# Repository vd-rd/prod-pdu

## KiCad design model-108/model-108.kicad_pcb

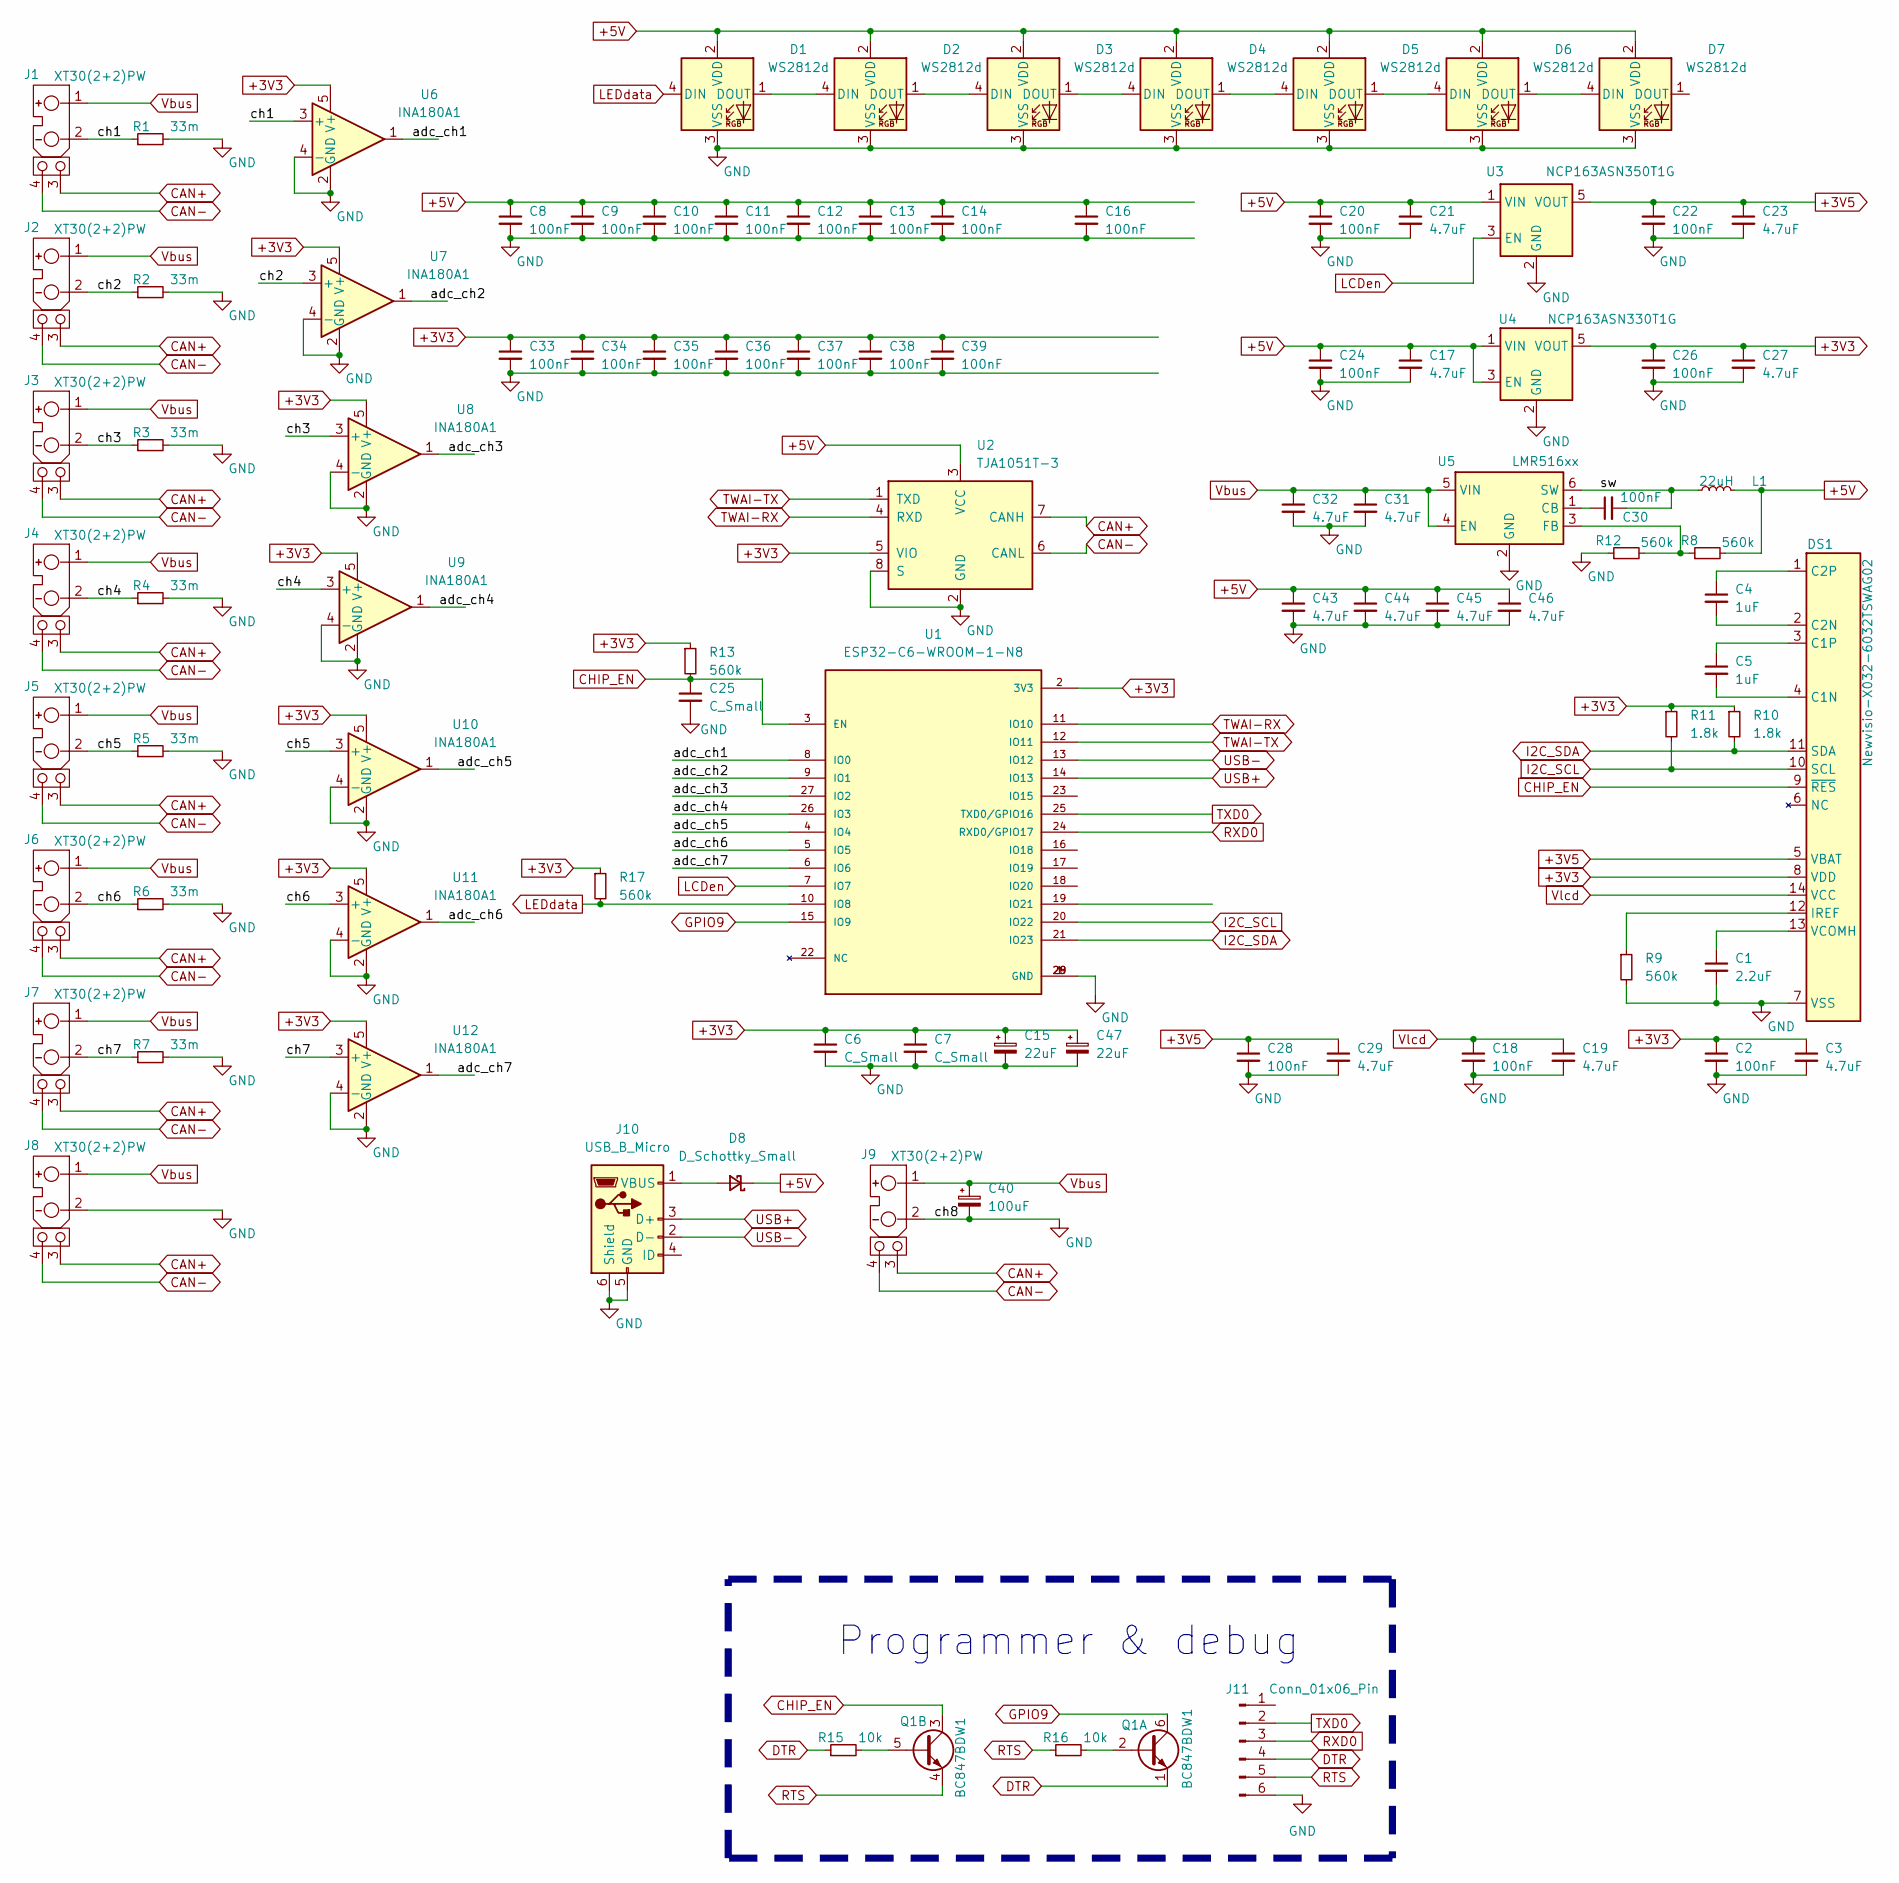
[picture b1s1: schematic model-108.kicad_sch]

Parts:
C1: 2.2uF; C_0603_1608Metric
C2, C8, C9, C10, C11, C12, C13, C14, C16, C18, C20, C22, C24, C26, C28, C30, C33, C34, C35, C36, C37, C38, C39: 100nF; C_0603_1608Metric
C3, C17, C19, C21, C23, C27, C29: 4.7uF; C_0603_1608Metric
C4, C5: 1uF; C_0603_1608Metric; Voltage 16V
C6, C7, C25: C_Small; C_0603_1608Metric
C15, C47: 22uF; CP_EIA-3216-10_Kemet-I
C31, C32, C43, C44, C45, C46: 4.7uF; C_0805_2012Metric
C40: 100uF; CP_Elec_8x5.4
D1, D2, D3, D4, D5, D6, D7: WS2812d; LED_D5.0mm-4_RGB
D8: D_Schottky_Small; D_SOD-123
DS1: Newvisio-X032-6032TSWAG02; OLED-60032D
J1, J2, J3, J4, J5, J6, J7, J8, J9: XT30(2+2)PW; AMASS_XT30(2+2)PW-M_P2.50mm_Horizontal
J10: USB_B_Micro; USB_Micro-B_Amphenol_10103594-0001LF_Horizontal
J11: Conn_01x06_Pin; PinHeader_1x06_P2.54mm_Vertical
L1: 22uH; L_Bourns_SRN8040TA
Q1: BC847BDW1; SOT-363_SC-70-6
R1, R2, R3, R4, R5, R6, R7: 33m; R_2512_6332Metric
R8, R9, R12, R13, R17: 560k; R_0603_1608Metric
R10, R11: 1.8k; R_0603_1608Metric
R15, R16: 10k; R_0402_1005Metric
U1: ESP32-C6-WROOM-1-N8; XCVR_ESP32-C6-WROOM-1-N8; PARTREV 1.0
U2: TJA1051T-3; SOIC-8_3.9x4.9mm_P1.27mm
U3: NCP163ASN350T1G; SOT-23-5
U4: NCP163ASN330T1G; SOT-23-5
U5: LMR516xx; TSOT-23-6
U6, U7, U8, U9, U10, U11, U12: INA180A1; SOT-23-5

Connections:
+3V3: C2.1, C3.1, C6.1, C7.1, C15.1, C26.1, C27.1, C33.1, C34.1, C35.1, C36.1, C37.1, C38.1, C39.1, C47.1, DS1.8 (VDD), R10.1, R11.1, R13.1, R17.1, U1.2 (3V3), U2.5 (VIO), U4.5 (VOUT), U6.5 (V+), U7.5 (V+), U8.5 (V+), U9.5 (V+), U10.5 (V+), U11.5 (V+), U12.5 (V+)
+3V5: C22.1, C23.1, C28.1, C29.1, DS1.5 (VBAT), U3.5 (VOUT)
+5V: C8.1, C9.1, C10.1, C11.1, C12.1, C13.1, C14.1, C16.1, C17.1, C20.1, C21.1, C24.1, C43.1, C44.1, C45.1, C46.1, D1.2 (VDD), D2.2 (VDD), D3.2 (VDD), D4.2 (VDD), D5.2 (VDD), D6.2 (VDD), D7.2 (VDD), D8.1 (K), L1.1, R8.2, U2.3 (VCC), U3.1 (VIN), U4.1 (VIN), U4.3 (EN)
/adc_ch1: U1.8 (IO0), U6.1
/adc_ch2: U1.9 (IO1), U7.1
/adc_ch3: U1.27 (IO2), U8.1
/adc_ch4: U1.26 (IO3), U9.1
/adc_ch5: U1.4 (IO4), U10.1
/adc_ch6: U1.5 (IO5), U11.1
/adc_ch7: U1.6 (IO6), U12.1
/ch1: J1.2, R1.1, U6.3 (+)
/ch2: J2.2, R2.1, U7.3 (+)
/ch3: J3.2, R3.1, U8.3 (+)
/ch4: J4.2, R4.1, U9.3 (+)
/ch5: J5.2, R5.1, U10.3 (+)
/ch6: J6.2, R6.1, U11.3 (+)
/ch7: J7.2, R7.1, U12.3 (+)
/sw: C30.2, L1.2, U5.6 (SW)
CAN+: J1.3, J2.3, J3.3, J4.3, J5.3, J6.3, J7.3, J8.3, J9.3, U2.7 (CANH)
CAN-: J1.4, J2.4, J3.4, J4.4, J5.4, J6.4, J7.4, J8.4, J9.4, U2.6 (CANL)
CHIP_EN: C25.1, DS1.9 (~RES), Q1.3 (C2), R13.2, U1.3 (EN)
DTR: J11.4, Q1.1 (E1), R15.1
GND: C1.2, C2.2, C3.2, C6.2, C7.2, C8.2, C9.2, C10.2, C11.2, C12.2, C13.2, C14.2, C15.2, C16.2, C17.2, C18.2, C19.2, C20.2, C21.2, C22.2, C23.2, C24.2, C25.2, C26.2, C27.2, C28.2, C29.2, C31.2, C32.2, C33.2, C34.2, C35.2, C36.2, C37.2, C38.2, C39.2, C40.2, C43.2, C44.2, C45.2, C46.2, C47.2, D1.3 (VSS), D2.3 (VSS), D3.3 (VSS), D4.3 (VSS), D5.3 (VSS), D6.3 (VSS), D7.3 (VSS), DS1.7 (VSS), J8.2, J9.2, J10.5 (GND), J10.6 (Shield), J11.6, R1.2, R2.2, R3.2, R4.2, R5.2, R6.2, R7.2, R9.2, R12.1, U1.1 (GND), U1.28 (GND), U1.29 (GND), U2.2 (GND), U2.8 (S), U3.2 (GND), U4.2 (GND), U5.2 (GND), U6.2 (GND), U6.4 (-), U7.2 (GND), U7.4 (-), U8.2 (GND), U8.4 (-), U9.2 (GND), U9.4 (-), U10.2 (GND), U10.4 (-), U11.2 (GND), U11.4 (-), U12.2 (GND), U12.4 (-)
GPIO9: Q1.6 (C1), U1.15 (IO9)
I2C_SCL: DS1.10 (SCL), R11.2, U1.20 (IO22)
I2C_SDA: DS1.11 (SDA), R10.2, U1.21 (IO23)
LCDen: U1.7 (IO7), U3.3 (EN)
LEDdata: D1.4 (DIN), R17.2, U1.10 (IO8)
unnamed: D1.1 (DOUT), D2.4 (DIN)
unnamed: D2.1 (DOUT), D3.4 (DIN)
unnamed: D3.1 (DOUT), D4.4 (DIN)
unnamed: D4.1 (DOUT), D5.4 (DIN)
unnamed: D5.1 (DOUT), D6.4 (DIN)
unnamed: D6.1 (DOUT), D7.4 (DIN)
unnamed: D8.2 (A), J10.1 (VBUS)
unnamed: C5.2, DS1.4 (C1N)
unnamed: C5.1, DS1.3 (C1P)
unnamed: C4.2, DS1.2 (C2N)
unnamed: C4.1, DS1.1 (C2P)
unnamed: DS1.12 (IREF), R9.1
unnamed: C1.1, DS1.13 (VCOMH)
unnamed: Q1.2 (B1), R16.2
unnamed: Q1.5 (B2), R15.2
unnamed: C30.1, U5.1 (CB)
unnamed: R8.1, R12.2, U5.3 (FB)
RTS: J11.5, Q1.4 (E2), R16.1
RXD0: J11.3, U1.24 (RXD0/GPIO17)
TWAI-RX: U1.11 (IO10), U2.4 (RXD)
TWAI-TX: U1.12 (IO11), U2.1 (TXD)
TXD0: J11.2, U1.25 (TXD0/GPIO16)
USB+: J10.3 (D+), U1.14 (IO13)
USB-: J10.2 (D-), U1.13 (IO12)
Vbus: C31.1, C32.1, C40.1, J1.1, J2.1, J3.1, J4.1, J5.1, J6.1, J7.1, J8.1, J9.1, U5.4 (EN), U5.5 (VIN)
Vlcd: C18.1, C19.1, DS1.14 (VCC)

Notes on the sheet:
Programmer & debug

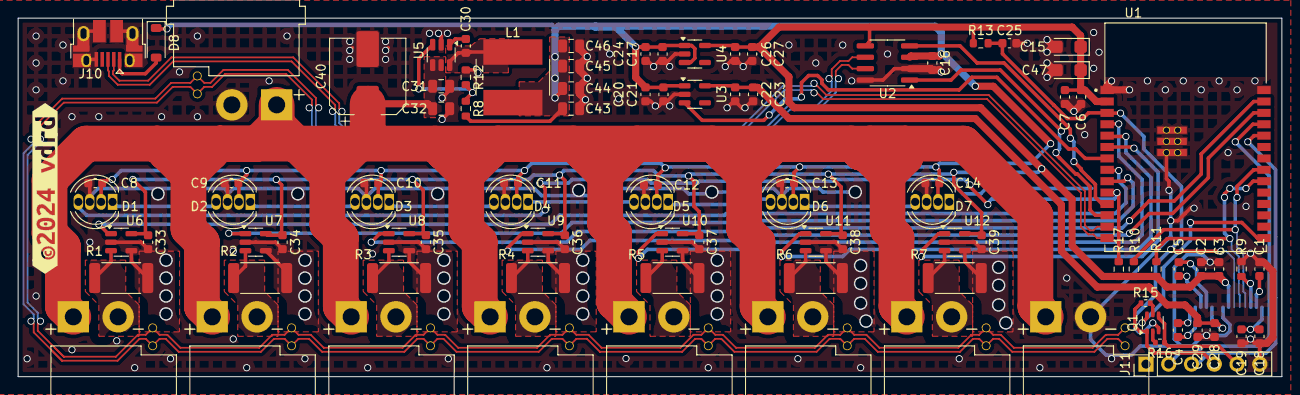
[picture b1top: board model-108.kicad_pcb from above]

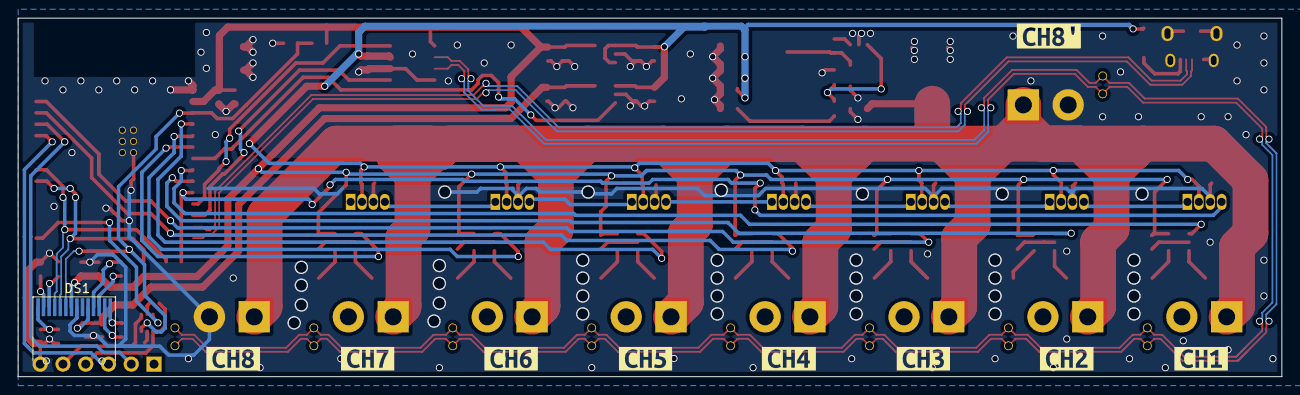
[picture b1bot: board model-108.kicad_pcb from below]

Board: 2 copper layers, 141.0 x 40.0 mm, 105 parts (10 on the bottom side), 54 nets.

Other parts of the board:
kibuzzard-66B0F7A6: G***; kibuzzard-66B0F7A6
kibuzzard-66B0F7B5: G***; kibuzzard-66B0F7B5
kibuzzard-66B0F7C1: G***; kibuzzard-66B0F7C1
kibuzzard-66B0F7CD: G***; kibuzzard-66B0F7CD
kibuzzard-66B0F7F4: G***; kibuzzard-66B0F7F4
kibuzzard-66B0F76D: G***; kibuzzard-66B0F76D
kibuzzard-66B0F77B: G***; kibuzzard-66B0F77B
kibuzzard-66B0F741: G***; kibuzzard-66B0F741
kibuzzard-66B0F792: G***; kibuzzard-66B0F792
kibuzzard-66B0F829: G***; kibuzzard-66B0F829

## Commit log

2024-08-05 board ready for fab
2024-11-16 add firmware boilerplate
